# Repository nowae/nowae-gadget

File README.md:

# nowae-gadget
Some useful gadget boards

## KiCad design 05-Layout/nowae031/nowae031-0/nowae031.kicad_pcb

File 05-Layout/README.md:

# nowae-gadget

In this folder you can find the boards design files of project.
* NOWAE022 - Christmas Tree Ball #1

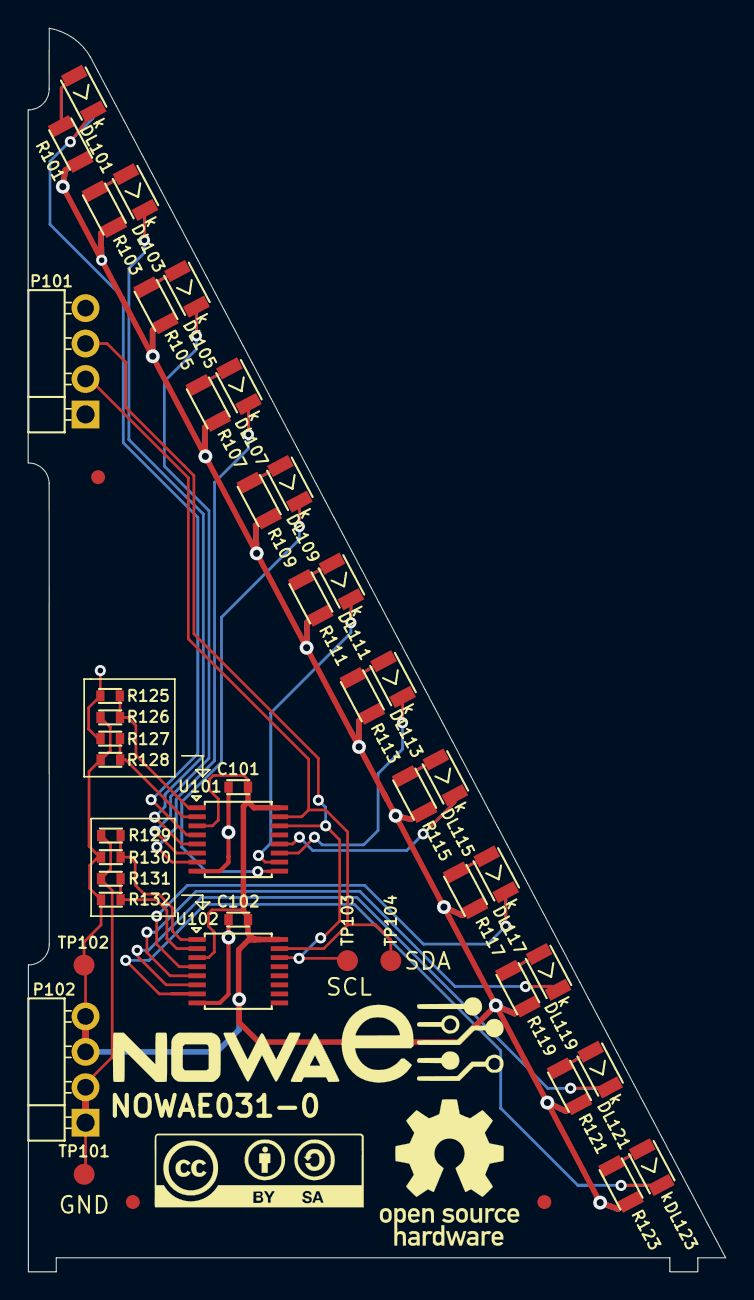
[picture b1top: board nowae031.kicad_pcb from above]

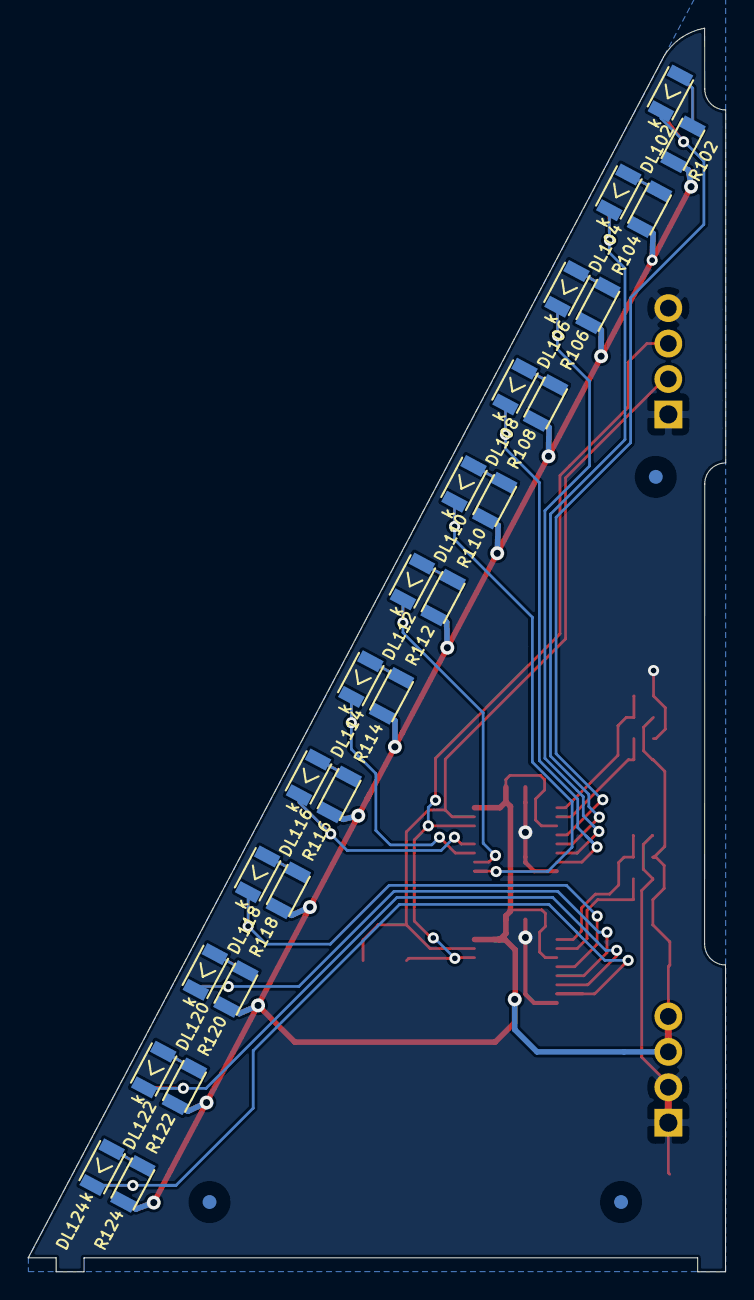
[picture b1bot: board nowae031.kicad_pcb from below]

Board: 2 copper layers, 50.0 x 89.2 mm, 72 parts (27 on the bottom side), 44 nets.

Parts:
C101, C102: 100n; CAPACITOR-0603
DL101, DL102, DL103, DL104, DL105, DL106, DL107, DL108, DL109, DL110, DL111, DL112, DL113, DL114, DL115, DL116, DL117, DL118, DL119, DL120, DL121, DL122, DL123, DL124: MISC; LED-1206
P101: COMM; CONN-STRIP-4x1-2.54-ANGLED
P102: SUPPLY; CONN-STRIP-4x1-2.54-ANGLED
R101, R102, R103, R104, R105, R106, R107, R108, R109, R110, R111, R112, R113, R114, R115, R116, R117, R118, R119, R120, R121, R122, R123, R124: 270; RESISTOR-1206
R125, R126, R127, R128, R129, R130, R131, R132: 0; RESISTOR-0603
TP101, TP102, TP103, TP104: TEST_POINT; TESTPOINT-1.5MM-SMD
U101, U102: TCA9554PWR; TSSOP16_4.4x5.0_0.65
VAL**: FIDUCIALMARK_1MM_3MM
VAL**#2, VAL**#3, VAL**#4, VAL**#5, VAL**#6: FIDUCIALMARK_1MM_3MM

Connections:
+3.3V: C101.2, C102.2, P102.3, P102.4, R101.2, R102.2, R103.2, R104.2, R105.2, R106.2, R107.2, R108.2, R109.2, R110.2, R111.2, R112.2, R113.2, R114.2, R115.2, R116.2, R117.2, R118.2, R119.2, R120.2, R121.2, R122.2, R123.2, R124.2, R126.1, R128.1, R130.1, R132.1, TP102.1, U101.3, U101.16, U102.3, U102.16
/BRANCH_SCL: P101.3, TP103.1, U101.14, U102.14
/BRANCH_SDA: P101.2, TP104.1, U101.15, U102.15
/B_LINE1: DL101.2, DL102.2, U101.4
/B_LINE2: DL103.2, DL104.2, U101.5
/B_LINE3: DL105.2, DL106.2, U101.6
/B_LINE4: DL107.2, DL108.2, U101.7
/B_LINE5: DL109.2, DL110.2, U101.9
/B_LINE6: DL111.2, DL112.2, U101.10
/B_LINE7: DL113.2, DL114.2, U101.11
/B_LINE8: DL115.2, DL116.2, U101.12
/B_LINE9: DL117.2, DL118.2, U102.4
/B_LINE10: DL119.2, DL120.2, U102.5
/B_LINE11: DL121.2, DL122.2, U102.6
/B_LINE12: DL123.2, DL124.2, U102.7
/MOD1A0: R125.2, R126.2, U101.1
/MOD1A1: R127.2, R128.2, U101.2
/MOD2A0: R129.2, R130.2, U102.1
/MOD2A1: R131.2, R132.2, U102.2
GND: C101.1, C102.1, P101.1, P101.4, P102.1, P102.2, R125.1, R127.1, R129.1, R131.1, TP101.1, U101.8, U102.8
unnamed: DL101.1, R101.1
unnamed: DL102.1, R102.1
unnamed: DL103.1, R103.1
unnamed: DL104.1, R104.1
unnamed: DL105.1, R105.1
unnamed: DL106.1, R106.1
unnamed: DL107.1, R107.1
unnamed: DL108.1, R108.1
unnamed: DL109.1, R109.1
unnamed: DL110.1, R110.1
unnamed: DL111.1, R111.1
unnamed: DL112.1, R112.1
unnamed: DL113.1, R113.1
unnamed: DL114.1, R114.1
unnamed: DL115.1, R115.1
unnamed: DL116.1, R116.1
unnamed: DL117.1, R117.1
unnamed: DL118.1, R118.1
unnamed: DL119.1, R119.1
unnamed: DL120.1, R120.1
unnamed: DL121.1, R121.1
unnamed: DL122.1, R122.1
unnamed: DL123.1, R123.1
unnamed: DL124.1, R124.1

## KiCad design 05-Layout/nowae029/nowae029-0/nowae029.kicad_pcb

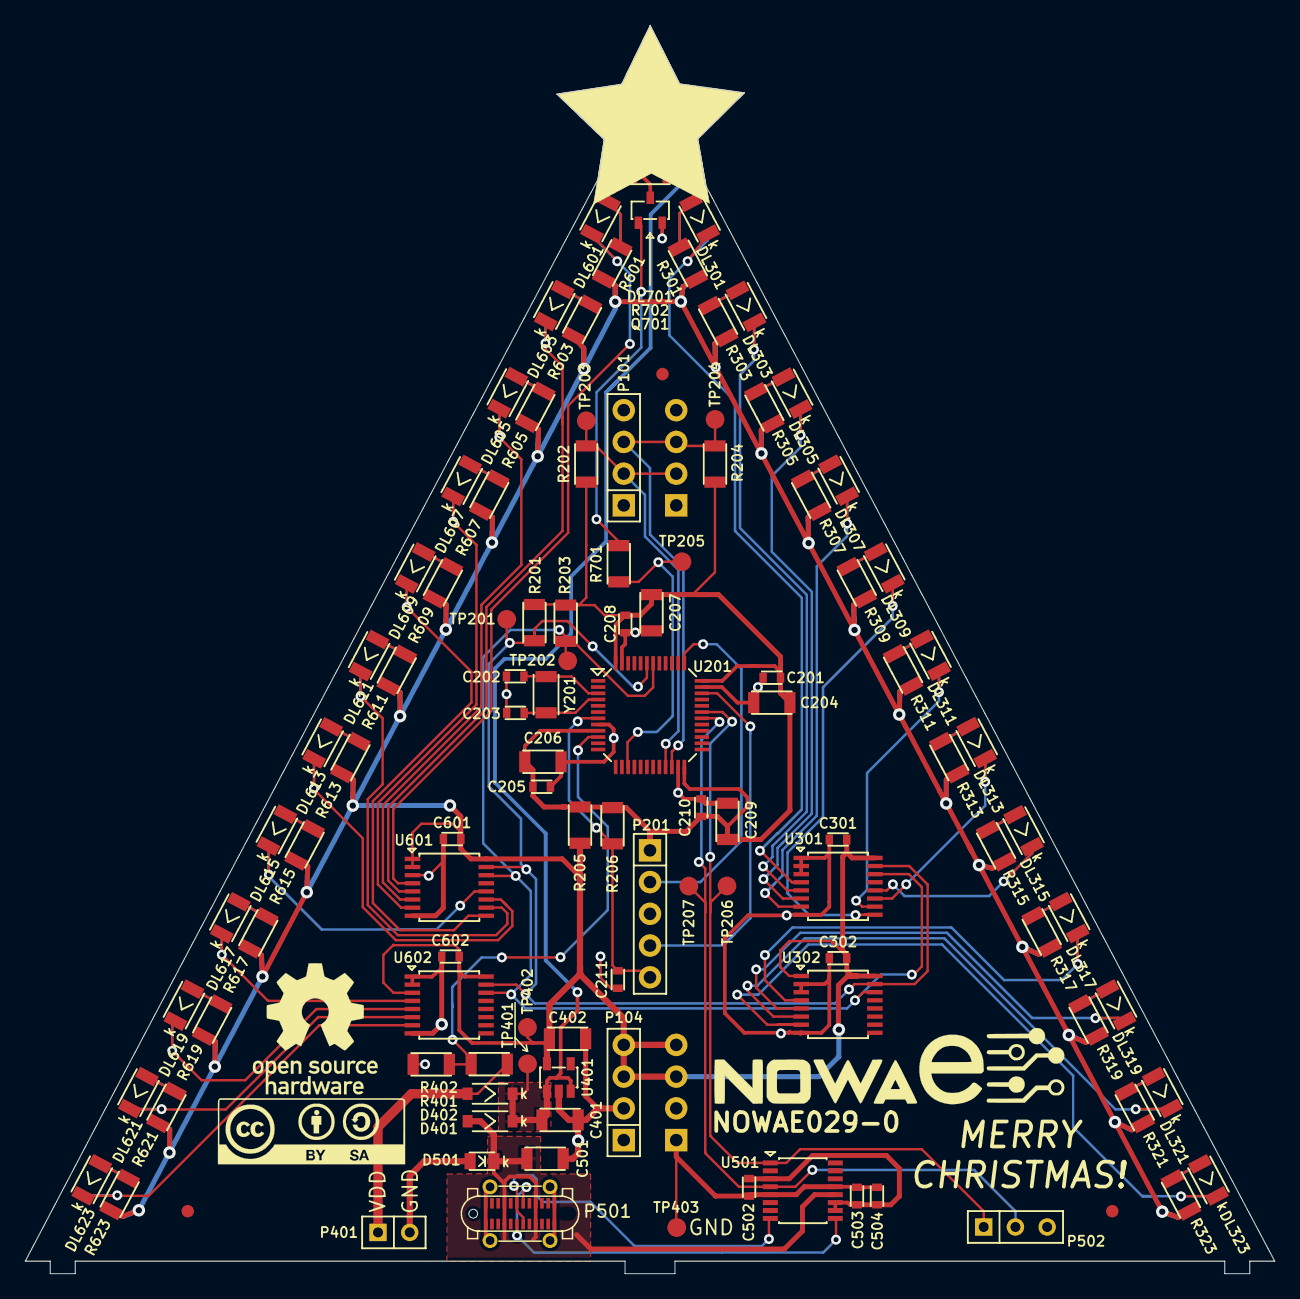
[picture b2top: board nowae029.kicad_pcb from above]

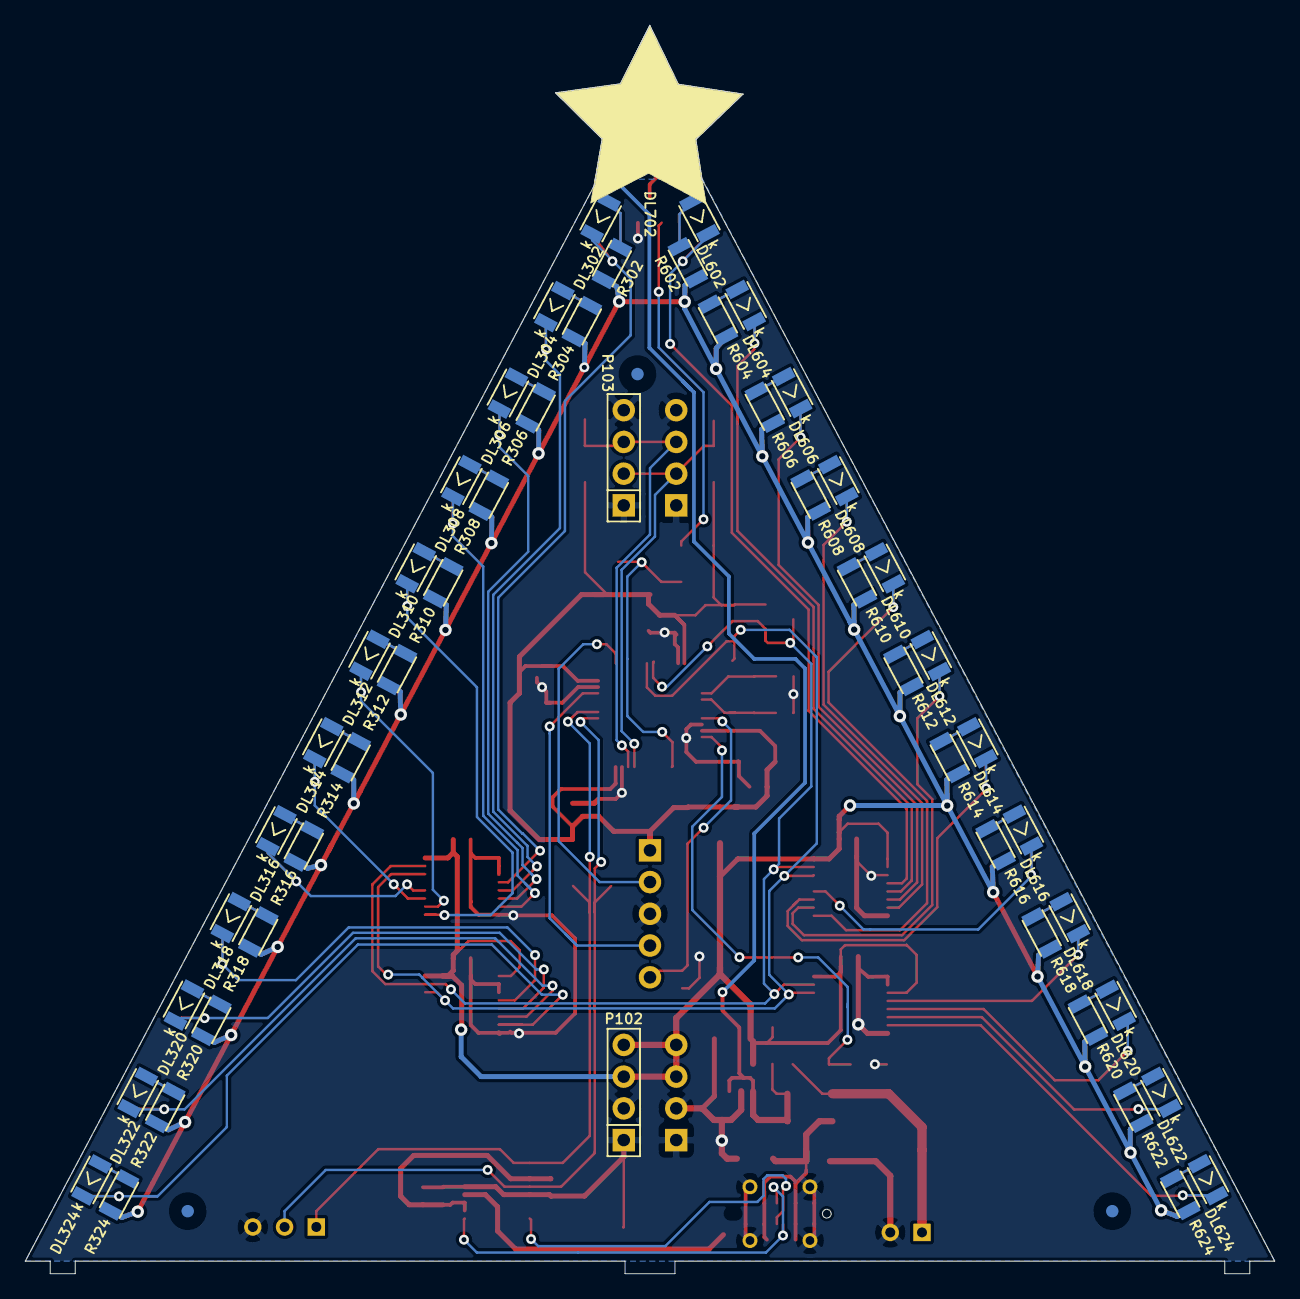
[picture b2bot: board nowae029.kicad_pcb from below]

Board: 2 copper layers, 100.0 x 99.9 mm, 165 parts (54 on the bottom side), 97 nets.

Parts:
C201, C205, C208, C210, C211, C301, C302, C502, C503, C504, C601, C602: 100n; CAPACITOR-0603
C202, C203: 15p; CAPACITOR-0603
C204, C206, C207, C209: 10u; CAPACITOR-1206
C401, C402: 1u; CAPACITOR-1206
C501: 4u7; CAPACITOR-1206
D401, D402: MBR0520; DIODE-SOD123
D501: ESDA25P35; DIODE-0805
DL301, DL302, DL303, DL304, DL305, DL306, DL307, DL308, DL309, DL310, DL311, DL312, DL313, DL314, DL315, DL316, DL317, DL318, DL319, DL320, DL321, DL322, DL323, DL324, DL601, DL602, DL603, DL604, DL605, DL606, DL607, DL608, DL609, DL610, DL611, DL612, DL613, DL614, DL615, DL616, DL617, DL618, DL619, DL620, DL621, DL622, DL623, DL624: MISC; LED-1206
DL701, DL702: WHITE; LED-WURTH-WL_SWTP_3014
P101: COMM_3; CONN-STRIP-4x1-2.54
P102: SUPPLY_3; CONN-STRIP-4x1-2.54
P103: COMM_4; CONN-STRIP-4x1-2.54
P104: SUPPLY_4; CONN-STRIP-4x1-2.54
P201: DEBUG; CONN-STRIP-5x1-2.54
P401: BATTERY; CONN-STRIP-2x1-2.54
P501: 632722110112; USB3.1-C_WE-632722110112
P502: UART; CONN-STRIP-3x1-2.54
Q701: BCW68GLT1G; SOT23-3
R201, R202, R203, R204: 4k7; RESISTOR-1206
R205: 0; RESISTOR-1206
R206: 10k; RESISTOR-1206
R301, R302, R303, R304, R305, R306, R307, R308, R309, R310, R311, R312, R313, R314, R315, R316, R317, R318, R319, R320, R321, R322, R323, R324, R601, R602, R603, R604, R605, R606, R607, R608, R609, R610, R611, R612, R613, R614, R615, R616, R617, R618, R619, R620, R621, R622, R623, R624: 270; RESISTOR-1206
R401, R402: 100k; RESISTOR-1206
R701, R702: RESISTOR; RESISTOR-1206
TP201, TP202, TP203, TP204, TP205, TP206, TP207, TP401, TP402, TP403: TEST_POINT; TESTPOINT-1.5MM-SMD
U201: STM32L073CBT6; LQFP48_7x7_0.5
U301, U302, U601, U602: TCA9554PWR; TSSOP16_4.4x5.0_0.65
U401: TLV70233DBV; SOT23-5
U501: FT230XS; SSOP16_3.9x4.9_0.635
VAL**: FIDUCIALMARK_1MM_3MM
VAL**#2, VAL**#3, VAL**#4, VAL**#5, VAL**#6: FIDUCIALMARK_1MM_3MM
Y201: 32768; CRYSTAL_1206

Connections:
+3.3V: C301.2, C302.2, C402.1, C601.2, C602.2, P102.3, P102.4, P104.3, P104.4, R205.1, R301.2, R302.2, R303.2, R304.2, R305.2, R306.2, R307.2, R308.2, R309.2, R310.2, R311.2, R312.2, R313.2, R314.2, R315.2, R316.2, R317.2, R318.2, R319.2, R320.2, R321.2, R322.2, R323.2, R324.2, R601.2, R602.2, R603.2, R604.2, R605.2, R606.2, R607.2, R608.2, R609.2, R610.2, R611.2, R612.2, R613.2, R614.2, R615.2, R616.2, R617.2, R618.2, R619.2, R620.2, R621.2, R622.2, R623.2, R624.2, TP402.1, U301.16, U302.1, U302.16, U401.5, U601.1, U601.2, U601.16, U602.3, U602.16
+VDD: C401.1, D401.2, D402.2, DL701.2, DL702.2, TP401.1, U401.1, U401.3
+VUSB: C501.1, D401.1, D501.2, P501.A4, P501.A9, P501.B4, P501.B9, U501.12
/B_EXT_SCL: P101.3, P103.3, R204.2, TP204.1, U201.22
/B_EXT_SDA: P101.2, P103.2, R202.2, TP203.1, U201.21
/Branch1/B1_LINE1: DL301.2, DL302.2, U301.4
/Branch1/B1_LINE2: DL303.2, DL304.2, U301.5
/Branch1/B1_LINE3: DL305.2, DL306.2, U301.6
/Branch1/B1_LINE4: DL307.2, DL308.2, U301.7
/Branch1/B1_LINE5: DL309.2, DL310.2, U301.9
/Branch1/B1_LINE6: DL311.2, DL312.2, U301.10
/Branch1/B1_LINE7: DL313.2, DL314.2, U301.11
/Branch1/B1_LINE8: DL315.2, DL316.2, U301.12
/Branch1/B1_LINE9: DL317.2, DL318.2, U302.4
/Branch1/B1_LINE10: DL319.2, DL320.2, U302.5
/Branch1/B1_LINE11: DL321.2, DL322.2, U302.6
/Branch1/B1_LINE12: DL323.2, DL324.2, U302.7
/Branch1/BRANCH1_SCL: R203.2, TP202.1, U201.42, U301.14, U302.14, U601.14, U602.14
/Branch1/BRANCH1_SDA: R201.2, TP201.1, U201.43, U301.15, U302.15, U601.15, U602.15
/Branch2/B2_LINE1: DL601.2, DL602.2, U601.4
/Branch2/B2_LINE2: DL603.2, DL604.2, U601.5
/Branch2/B2_LINE3: DL605.2, DL606.2, U601.6
/Branch2/B2_LINE4: DL607.2, DL608.2, U601.7
/Branch2/B2_LINE5: DL609.2, DL610.2, U601.9
/Branch2/B2_LINE6: DL611.2, DL612.2, U601.10
/Branch2/B2_LINE7: DL613.2, DL614.2, U601.11
/Branch2/B2_LINE8: DL615.2, DL616.2, U601.12
/Branch2/B2_LINE9: DL617.2, DL618.2, U602.4
/Branch2/B2_LINE10: DL619.2, DL620.2, U602.5
/Branch2/B2_LINE11: DL621.2, DL622.2, U602.6
/Branch2/B2_LINE12: DL623.2, DL624.2, U602.7
/Communication/COMM_RX: P502.2, TP207.1, U201.30, U501.4
/Communication/COMM_TX: P502.1, TP206.1, U201.31, U501.1
/Communication/FTDI_VCC: C502.1, C503.1, C504.1, U501.3, U501.10, U501.11
/Microcontroller/RESET: C211.2, P201.5, R206.2, U201.7
/Microcontroller/STAR: R701.1, TP205.1, U201.15
/Microcontroller/SWCLK: P201.2, U201.37
/Microcontroller/SWDIO: P201.4, U201.34
/Microcontroller/VDD_MCU: C201.1, C204.1, C205.1, C206.1, C207.1, C208.1, C209.1, C210.1, P201.1, R201.1, R202.1, R203.1, R204.1, R205.2, R206.1, U201.9, U201.24, U201.36, U201.48
/Power Supply/BATTERY_STATUS: R401.2, R402.1, U201.10
GND: C201.2, C202.2, C203.2, C204.2, C205.2, C206.2, C207.2, C208.2, C209.2, C210.2, C211.1, C301.1, C302.1, C401.2, C402.2, C501.2, C502.2, C503.2, C504.2, C601.1, C602.1, D501.1, P101.1, P101.4, P102.1, P102.2, P103.1, P103.4, P104.1, P104.2, P201.3, P401.2, P501.A1, P501.A12, P501.B1, P501.B12, P501.S1, P502.3, Q701.2, R402.2, TP403.1, U201.8, U201.23, U201.35, U201.47, U301.1, U301.2, U301.3, U301.8, U302.2, U302.3, U302.8, U401.2, U501.5, U501.13, U601.3, U601.8, U602.1, U602.2, U602.8
unnamed: C202.1, U201.3, Y201.1
unnamed: C203.1, U201.4, Y201.2
unnamed: D402.1, P401.1, R401.1
unnamed: DL301.1, R301.1
unnamed: DL302.1, R302.1
unnamed: DL303.1, R303.1
unnamed: DL304.1, R304.1
unnamed: DL305.1, R305.1
unnamed: DL306.1, R306.1
unnamed: DL307.1, R307.1
unnamed: DL308.1, R308.1
unnamed: DL309.1, R309.1
unnamed: DL310.1, R310.1
unnamed: DL311.1, R311.1
unnamed: DL312.1, R312.1
unnamed: DL313.1, R313.1
unnamed: DL314.1, R314.1
unnamed: DL315.1, R315.1
unnamed: DL316.1, R316.1
unnamed: DL317.1, R317.1
unnamed: DL318.1, R318.1
unnamed: DL319.1, R319.1
unnamed: DL320.1, R320.1
unnamed: DL321.1, R321.1
unnamed: DL322.1, R322.1
unnamed: DL323.1, R323.1
unnamed: DL324.1, R324.1
unnamed: DL601.1, R601.1
unnamed: DL602.1, R602.1
unnamed: DL603.1, R603.1
unnamed: DL604.1, R604.1
unnamed: DL605.1, R605.1
unnamed: DL606.1, R606.1
unnamed: DL607.1, R607.1
unnamed: DL608.1, R608.1
unnamed: DL609.1, R609.1
unnamed: DL610.1, R610.1
unnamed: DL611.1, R611.1
unnamed: DL612.1, R612.1
unnamed: DL613.1, R613.1
unnamed: DL614.1, R614.1
unnamed: DL615.1, R615.1
unnamed: DL616.1, R616.1
unnamed: DL617.1, R617.1
unnamed: DL618.1, R618.1
unnamed: DL619.1, R619.1
unnamed: DL620.1, R620.1
unnamed: DL621.1, R621.1
unnamed: DL622.1, R622.1
unnamed: DL623.1, R623.1
unnamed: DL624.1, R624.1
unnamed: DL701.1, DL702.1, R702.1
unnamed: P501.A6, P501.B6, U501.8
unnamed: P501.A7, P501.B7, U501.9
unnamed: Q701.1, R701.2
unnamed: Q701.3, R702.2

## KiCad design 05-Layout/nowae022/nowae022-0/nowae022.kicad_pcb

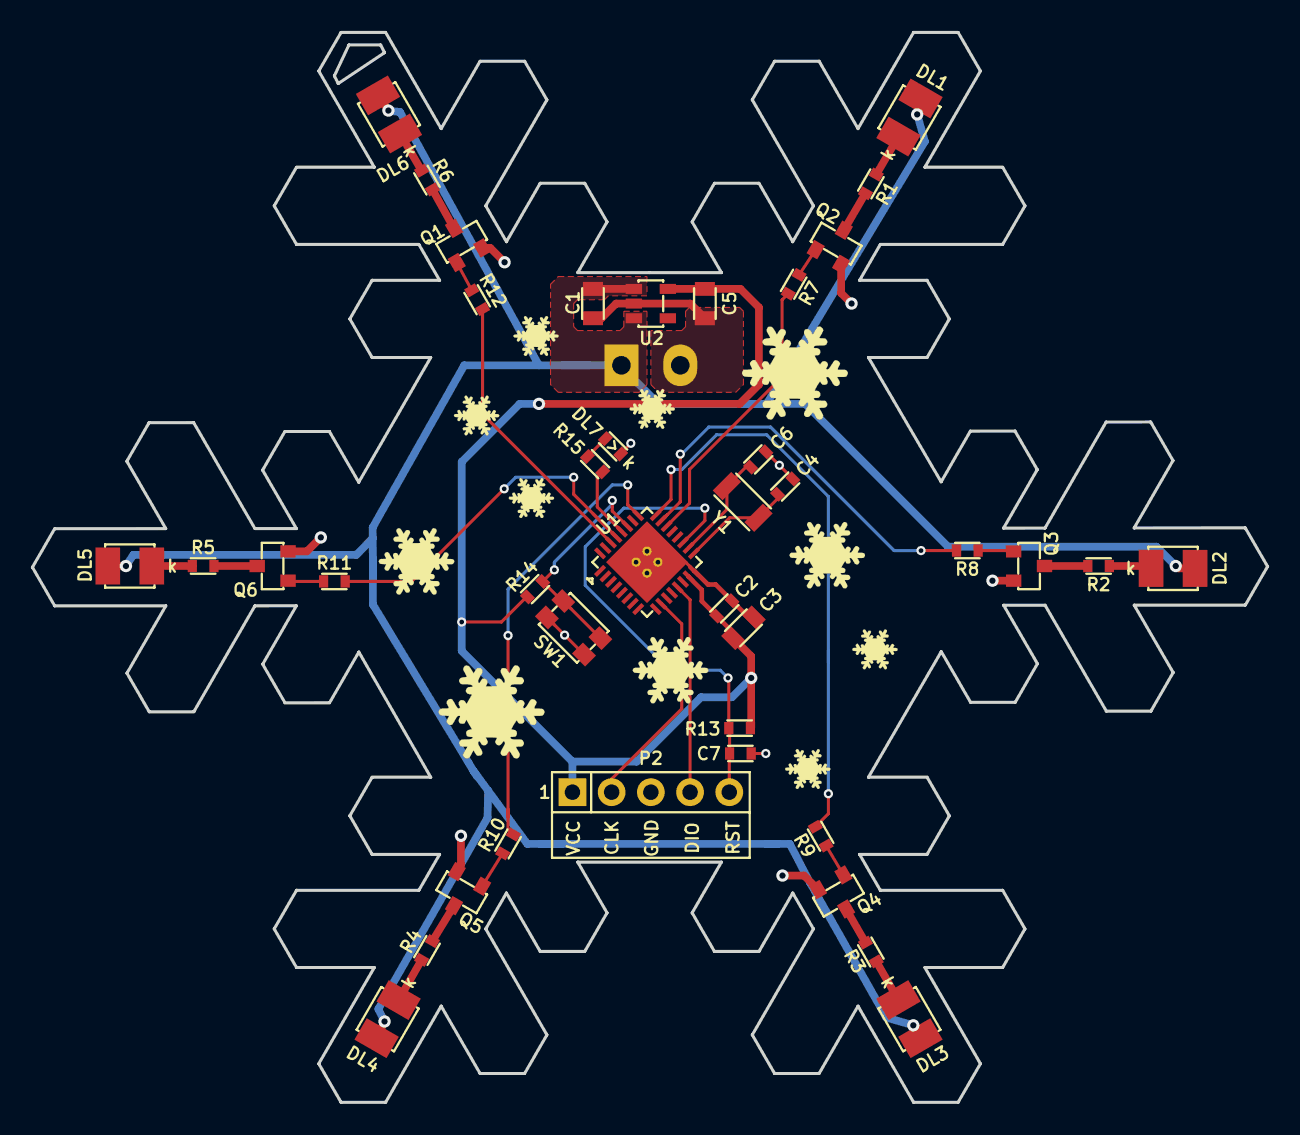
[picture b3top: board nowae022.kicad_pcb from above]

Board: 2 copper layers, 80.0 x 69.3 mm, 41 parts (1 on the bottom side), 35 nets.

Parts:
C1: 1u; CAPACITOR-0805
C2, C7: 100n; CAPACITOR-0603
C3: 10u; CAPACITOR-0805
C4, C6: 15p; CAPACITOR-0603
C5: 2u2; CAPACITOR-0805
DL1, DL2, DL3, DL4, DL5, DL6: RED; LED-WURTH-WL_SMTW_3528
DL7: GREEN; LED-0603
P1: SUPPLY; CONN-MKDS1_2-3.81
P2: SWD; CONN-STRIP-5x1-2.54
Q1, Q2, Q3, Q4, Q5, Q6: BCW66GLT; SOT23-3
R1, R2, R3, R4, R5, R6: 680; RESISTOR-0603
R7, R8, R9, R10, R11, R12: 1k2; RESISTOR-0603
R13, R14: 10k; RESISTOR-0603
R15: 270; RESISTOR-0603
SW1: BUTTON-WE_434153017835; BUTTON-WE-434153017835
U1: MKL15Z128VFM4; QFN32_5x5_0.5_32+1
U2: TPS70933DBV; SOT23-5
Y1: 32768; CRYSTAL-1206

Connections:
+3.3V: C2.1, C3.1, C5.1, P2.1, R13.1, R14.1, U1.15, U2.5
+VIN: C1.1, DL1.2, DL2.2, DL3.2, DL4.2, DL5.2, DL6.2, P1.1, U2.1, U2.3
/BALL_LED1: R7.2, U1.22
/BALL_LED2: R8.2, U1.23
/BALL_LED3: R9.2, U1.24
/BALL_LED4: R10.2, U1.25
/BALL_LED5: R11.2, U1.29
/BALL_LED6: R12.2, U1.30
/MCU_PROG: R14.2, SW1.2, SW1.4, U1.27
/MCU_STATUS: R15.2, U1.28
/RESET: C7.1, P2.5, R13.2, U1.19
/SWCLK: P2.2, U1.10
/SWDIO: P2.4, U1.13
GND: C1.2, C2.2, C3.2, C4.2, C5.2, C6.2, C7.2, DL7.2, P1.2, P2.3, Q1.2, Q2.2, Q3.2, Q4.2, Q5.2, Q6.2, SW1.1, SW1.3, U1.16, U1.EP, U2.2
unnamed: C4.1, U1.17, Y1.1
unnamed: C6.1, U1.18, Y1.2
unnamed: DL1.1, R1.1
unnamed: DL2.1, R2.1
unnamed: DL3.1, R3.1
unnamed: DL4.1, R4.1
unnamed: DL5.1, R5.1
unnamed: DL6.1, R6.1
unnamed: DL7.1, R15.1
unnamed: Q1.1, R12.1
unnamed: Q1.3, R6.2
unnamed: Q2.1, R7.1
unnamed: Q2.3, R1.2
unnamed: Q3.1, R8.1
unnamed: Q3.3, R2.2
unnamed: Q4.1, R9.1
unnamed: Q4.3, R3.2
unnamed: Q5.1, R10.1
unnamed: Q5.3, R4.2
unnamed: Q6.1, R11.1
unnamed: Q6.3, R5.2

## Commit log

2018-11-14 Added project structure (nowae022-0)
2018-11-15 WiP on schematic (nowae022-0)
2018-11-15 Added PCB file with Christmas Tree Ball edge cuts (nowae022-0)
2018-11-16 Ended schematic (nowae022-0)
2018-11-16 Added netlist (nowae022-0)
2018-11-16 WiP components placement(nowae022-0)
2018-11-16 WiP components placement and routing (nowae022-0)
2018-11-18 WiP routing (nowae022-0)
2018-11-19 Routing ended (nowae022-0)
2018-11-20 Fixed components silkscreen and fab (nowae022-0)
2018-11-20 Added some snowflake picture on silkscreen (nowae022-0)
2018-11-20 Fixed PCB silkscreen (nowae022-0)
2018-11-20 Added archive with gerber files (nowae022-0)
2018-11-22 Added NOWAE022-0 BOM, revision 0 (nowae022-0)
2018-11-22 Fixed worksheet informations and added schematic file into production directory (nowae022-0)
2018-11-23 Fixed BOM (nowae022-0)
2018-11-23 Fixed worksheet informations on PCB
2018-11-23 Added assembly informations (nowae022-0)
2018-11-27 Added firmware project for Christmas Tree Ball
2018-11-27 Added libohiboard submodule
2018-11-27 Added first project setting
2018-12-04 WiP Update of libohiboard
2018-12-23 Added nowae022-1 (nowae022-1) Added voltage divider for LDO enable pin (nowae022-1) Added pull-up resistor for SWDIO signal (nowae022-1)
2018-12-23 Annotated components (nowae022-1)
2019-10-21 Moved libohiboard outside the firmware project
2019-10-21 updated libohiboard
2019-10-21 moved libohiboard folder outside the project
2019-10-21 libohiboard updated.
2019-10-22 moved board.h file into profiles folder
2019-10-22 First test
2019-10-22 Added ignore file for debug folder
2019-11-11 Working on first test with timer free counter
2019-11-12 First usable leds game.
2020-09-14 Added file project
2020-09-23 First idea of Christmas Tree, the NOWAE gadget for 2020
2020-09-24 Start works on schematic
2020-09-24 WiP on microcontroller
2020-09-25 Designed branch connections and leds (branch1)
2020-09-25 Working on comm page
2020-09-27 Fixed communication page
2020-09-27 Fixed power supply page
2020-09-28 Fixed all parts
2020-09-28 Schematic annotations
2020-09-28 WiP: PCB components placing
2020-09-29 WiP: components placing
2020-09-29 Removed unused LEDs
2020-09-30 WiP: components placing Added some footprints
2020-10-01 WiP: I don't like the LEDs position...
2020-10-02 WiP: PCB removed some LEDs and placed in other way the others
2020-10-07 Removed LEDs, added star page, WiP PCB
2020-10-07 WiP PCB TODO: resistors value into star page
2020-10-07 WiP: GND connections
2020-10-08 Added test point footprint. PCB route ended!
2020-10-08 Added fiducial marker
2020-10-08 PCB End! TODO: production documents.
2020-10-09 small fix
2020-10-09 Added assembly documentstion
2020-10-09 Added gerber files
2020-10-09 Fixed schematic, added prduction PDF
2020-10-12 Added BOM
2020-10-13 Added schematic, netlist and started PCB
2020-10-14 WiP on PCB
2020-10-15 Added assembly documentations
2020-10-15 Added final schematic of NOWAE031-0
2020-10-19 Fixed connector versus NOWAE029 and generated new gerber files.
2020-11-30 Added submodules
2020-11-30 Added project
2020-12-02 Started working on TCA9554 driver
2020-12-02 update libohiboard
2020-12-05 Removed driver files. They will be moved into submodules.
2020-12-05 Added TCA9554 submodule
2020-12-13 submodules update
2020-12-13 Started working on application
2020-12-13 Added scheduler
2020-12-13 Working on hardware profile
2020-12-13 Added gpio expander controller and pins for each branch
2020-12-14 Testing code...
2020-12-15 I2C communication works
